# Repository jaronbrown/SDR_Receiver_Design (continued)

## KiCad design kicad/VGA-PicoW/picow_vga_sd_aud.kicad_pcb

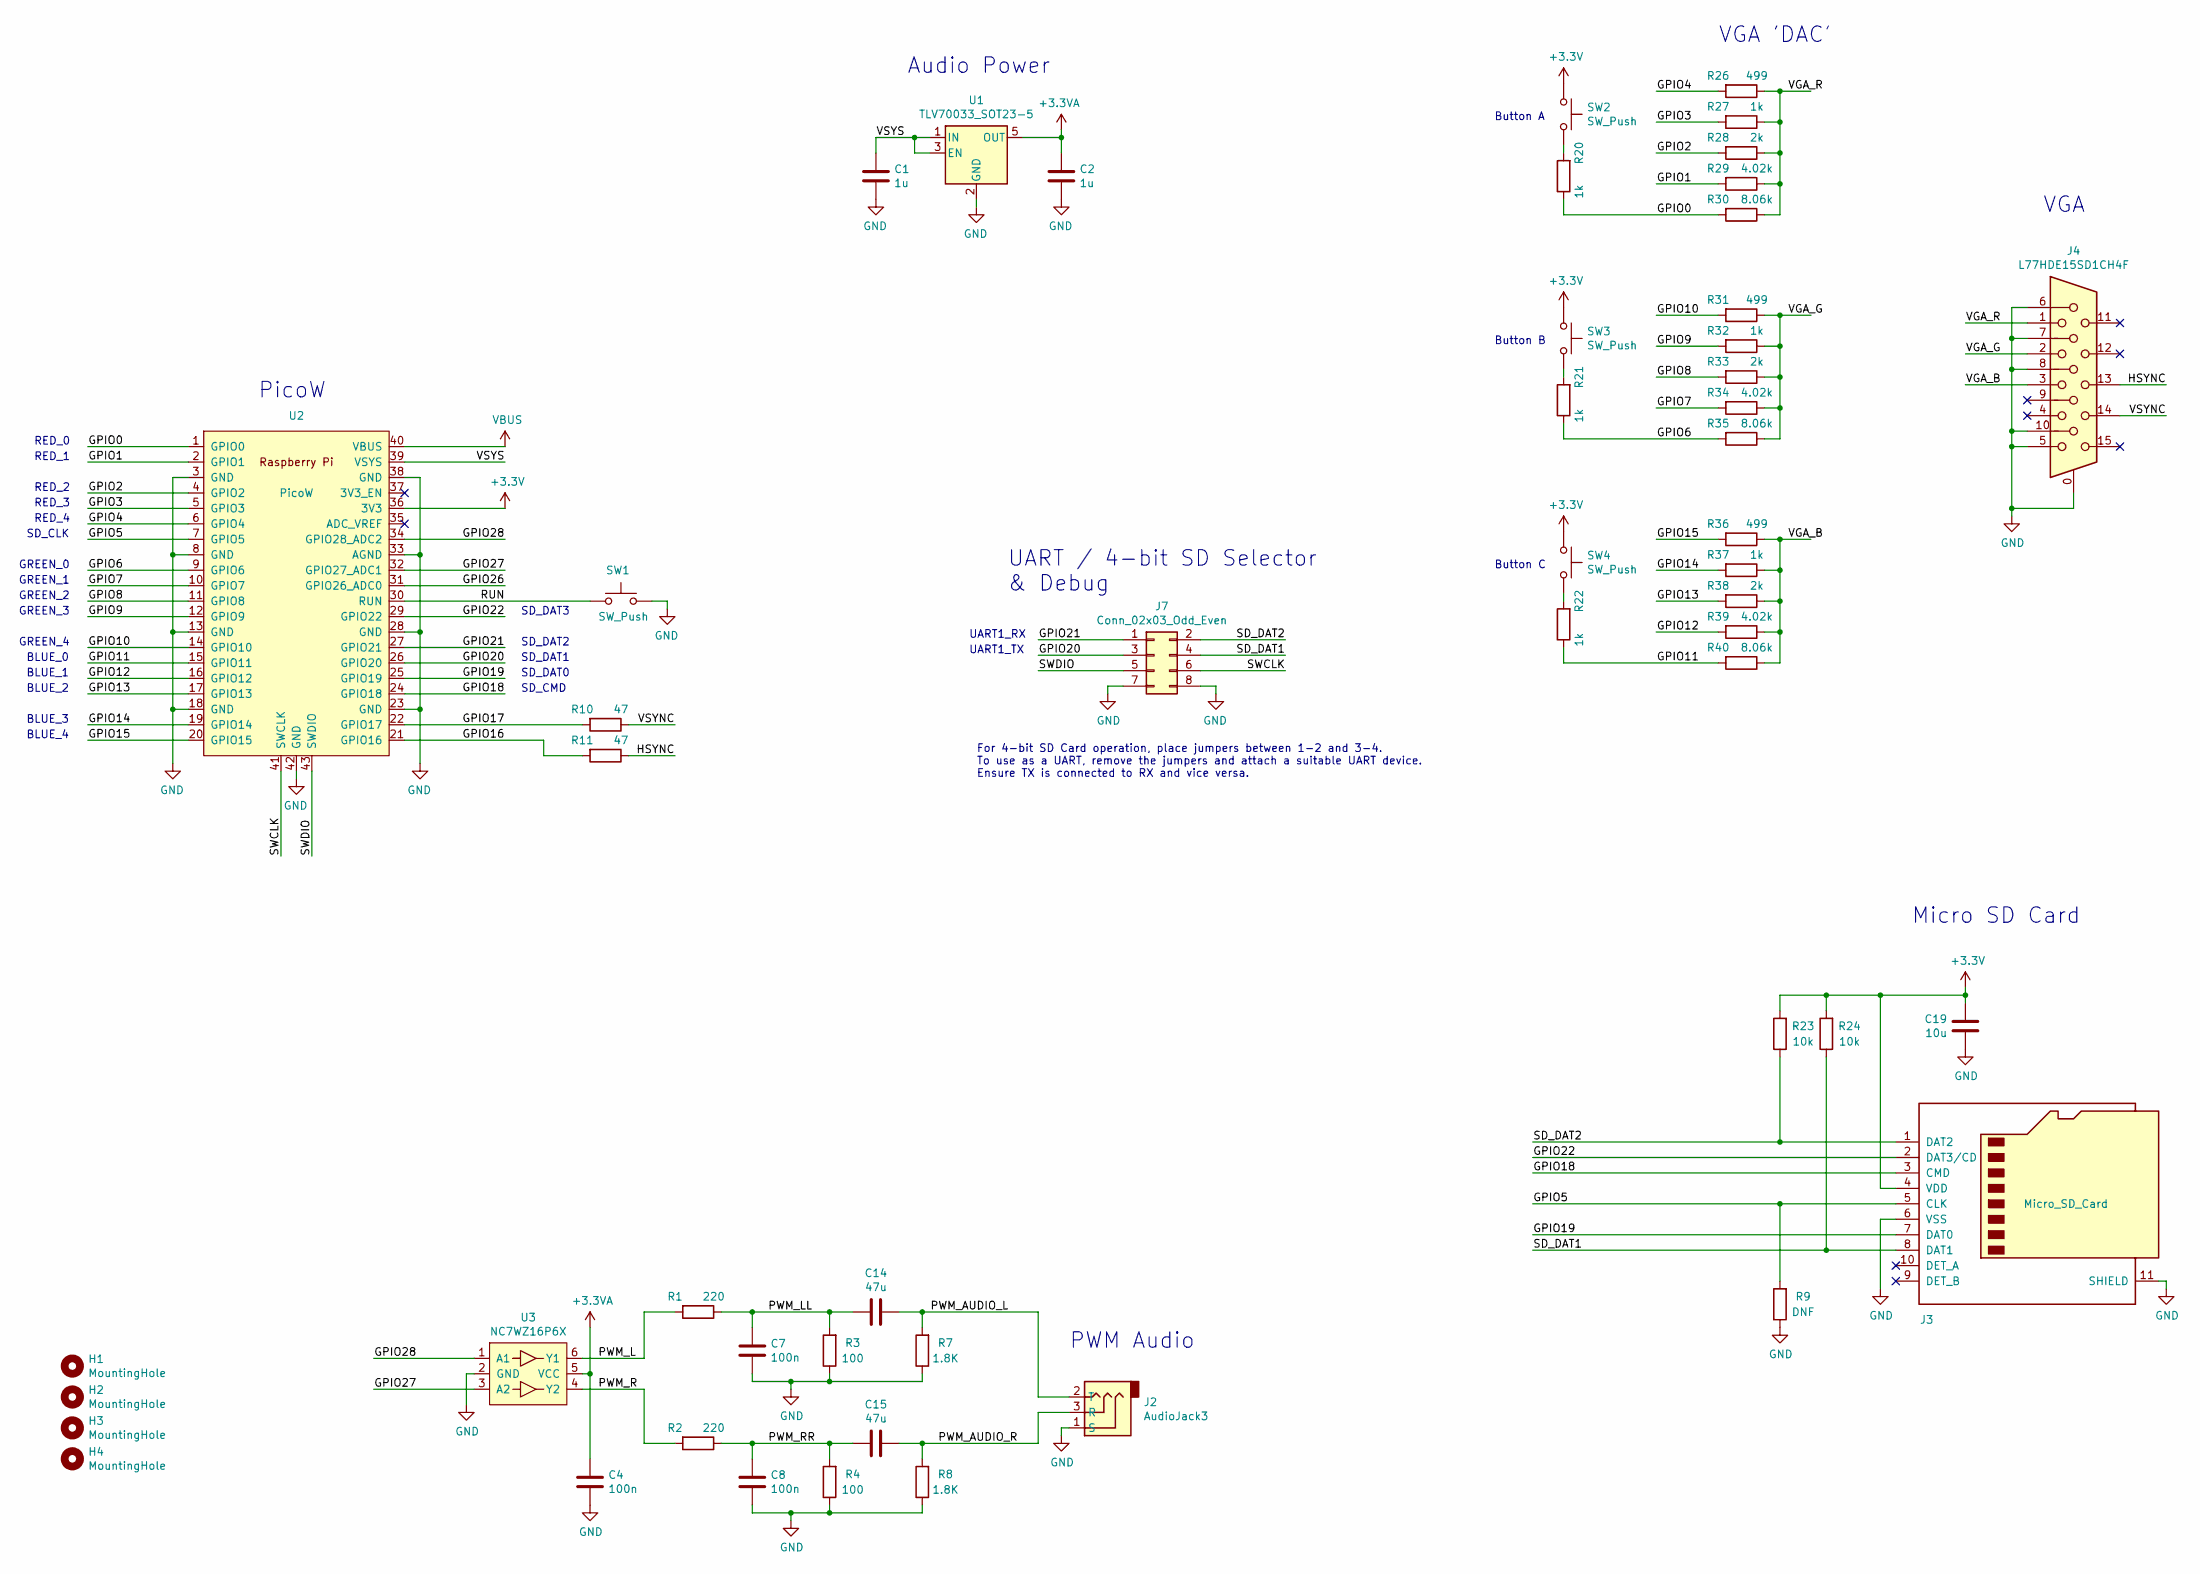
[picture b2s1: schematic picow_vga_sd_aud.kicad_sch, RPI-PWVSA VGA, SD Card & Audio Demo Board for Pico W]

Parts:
C1, C2: 1u; C_0603_1608Metric
C4, C7, C8: 100n; C_0402_1005Metric
C14, C15: 47u; C_0805_2012Metric
C19: 10u; C_0603_1608Metric
H1, H2, H3, H4: MountingHole; MountingHole_2.7mm_M2.5
J2: AudioJack3; CUI_SJ-3523-audio-jack
J3: Micro_SD_Card; microSD_HC_Molex_104031-0811
J4: L77HDE15SD1CH4F; DSUB-15-L77HDE15SD1CH4F
J7: Conn_02x03_Odd_Even; PinHeader_2x04_P2.54mm_Vertical
R1, R2: 220; R_0402_1005Metric
R3, R4: 100; R_0402_1005Metric
R7, R8: 1.8K; R_0402_1005Metric
R9: DNF; R_0402_1005Metric
R10, R11: 47; R_0402_1005Metric
R20, R21, R22, R27, R32, R37: 1k; R_0402_1005Metric
R23, R24: 10k; R_0402_1005Metric
R26, R31, R36: 499; R_0402_1005Metric
R28, R33, R38: 2k; R_0402_1005Metric
R29, R34, R39: 4.02k; R_0402_1005Metric
R30, R35, R40: 8.06k; R_0402_1005Metric
SW1, SW2, SW3, SW4: SW_Push; SW_Push_1P1T_NO_Vertical_Wuerth_434133025816
U1: TLV70033_SOT23-5; SOT-23-5
U2: PicoW; RPi_PicoW_SMD_TH
U3: NC7WZ16P6X; SOT-363_SC-70-6

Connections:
+3.3VA: C2.1, C4.1, U1.5 (OUT), U3.5 (VCC)
+3V3: C19.1, J3.4 (VDD), R23.2, R24.2, SW2.1, SW3.1, SW4.1, U2.36 (3V3)
/GPIO0: R20.1, R30.2, U2.1 (GPIO0)
/GPIO1: R29.2, U2.2 (GPIO1)
/GPIO2: R28.2, U2.4 (GPIO2)
/GPIO3: R27.2, U2.5 (GPIO3)
/GPIO4: R26.2, U2.6 (GPIO4)
/GPIO5: J3.5 (CLK), R9.2, U2.7 (GPIO5)
/GPIO6: R21.1, R35.2, U2.9 (GPIO6)
/GPIO7: R34.2, U2.10 (GPIO7)
/GPIO8: R33.2, U2.11 (GPIO8)
/GPIO9: R32.2, U2.12 (GPIO9)
/GPIO10: R31.2, U2.14 (GPIO10)
/GPIO11: R22.1, R40.2, U2.15 (GPIO11)
/GPIO12: R39.2, U2.16 (GPIO12)
/GPIO13: R38.2, U2.17 (GPIO13)
/GPIO14: R37.2, U2.19 (GPIO14)
/GPIO15: R36.2, U2.20 (GPIO15)
/GPIO16: R11.2, U2.21 (GPIO16)
/GPIO17: R10.2, U2.22 (GPIO17)
/GPIO18: J3.3 (CMD), U2.24 (GPIO18)
/GPIO19: J3.7 (DAT0), U2.25 (GPIO19)
/GPIO20: J7.3, U2.26 (GPIO20)
/GPIO21: J7.1, U2.27 (GPIO21)
/GPIO22: J3.2 (DAT3/CD), U2.29 (GPIO22)
/GPIO26: U2.31 (GPIO26_ADC0)
/GPIO27: U2.32 (GPIO27_ADC1), U3.3 (A2)
/GPIO28: U2.34 (GPIO28_ADC2), U3.1 (A1)
/HSYNC: J4.13, R11.1
/PWM_AUDIO_L: C14.1, J2.2 (T), R7.2
/PWM_AUDIO_R: C15.1, J2.3 (R), R8.2
/PWM_L: R1.2, U3.6 (Y1)
/PWM_LL: C7.1, C14.2, R1.1, R3.2
/PWM_R: R2.2, U3.4 (Y2)
/PWM_RR: C8.1, C15.2, R2.1, R4.2
/RUN: SW1.1, U2.30 (RUN)
/SD_DAT1: J3.8 (DAT1), J7.4, R24.1
/SD_DAT2: J3.1 (DAT2), J7.2, R23.1
/SWCLK: J7.6, U2.41 (SWCLK)
/SWDIO: J7.5, U2.43 (SWDIO)
/VGA_B: J4.3, R36.1, R37.1, R38.1, R39.1, R40.1
/VGA_G: J4.2, R31.1, R32.1, R33.1, R34.1, R35.1
/VGA_R: J4.1, R26.1, R27.1, R28.1, R29.1, R30.1
/VSYNC: J4.14, R10.1
/VSYS: C1.1, U1.1 (IN), U1.3 (EN), U2.39 (VSYS)
GND: C1.2, C2.2, C4.2, C7.2, C8.2, C19.2, J2.1 (S), J3.6 (VSS), J3.11 (SHIELD), J4.0, J4.5, J4.6, J4.7, J4.8, J4.10, J7.7, J7.8, R3.1, R4.1, R7.1, R8.1, R9.1, SW1.2, U1.2 (GND), U2.3 (GND), U2.8 (GND), U2.13 (GND), U2.18 (GND), U2.23 (GND), U2.28 (GND), U2.33 (AGND), U2.38 (GND), U2.42 (GND), U3.2 (GND)
unnamed: R20.2, SW2.2
unnamed: R21.2, SW3.2
unnamed: R22.2, SW4.2
VBUS: U2.40 (VBUS)

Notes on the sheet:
GREEN_0
RED_3
RED_1
SD_DAT2
Button A
VGA
SD_CLK
BLUE_4
BLUE_0
UART1_TX
SD_DAT1
RED_4
PicoW
For 4-bit SD Card operation, place jumpers between 1-2 and 3-4. To use as a UART, remove the jumpers and attach a suitable UART device. Ensure TX is connected to RX and vice versa.
UART1_RX
VGA 'DAC'
Button B
Button C
GREEN_1
UART / 4-bit SD Selector & Debug
SD_DAT0
BLUE_3
SD_CMD
SD_DAT3
Micro SD Card
GREEN_4
RED_2
GREEN_2
Audio Power
PWM Audio
BLUE_1
GREEN_3
BLUE_2
RED_0

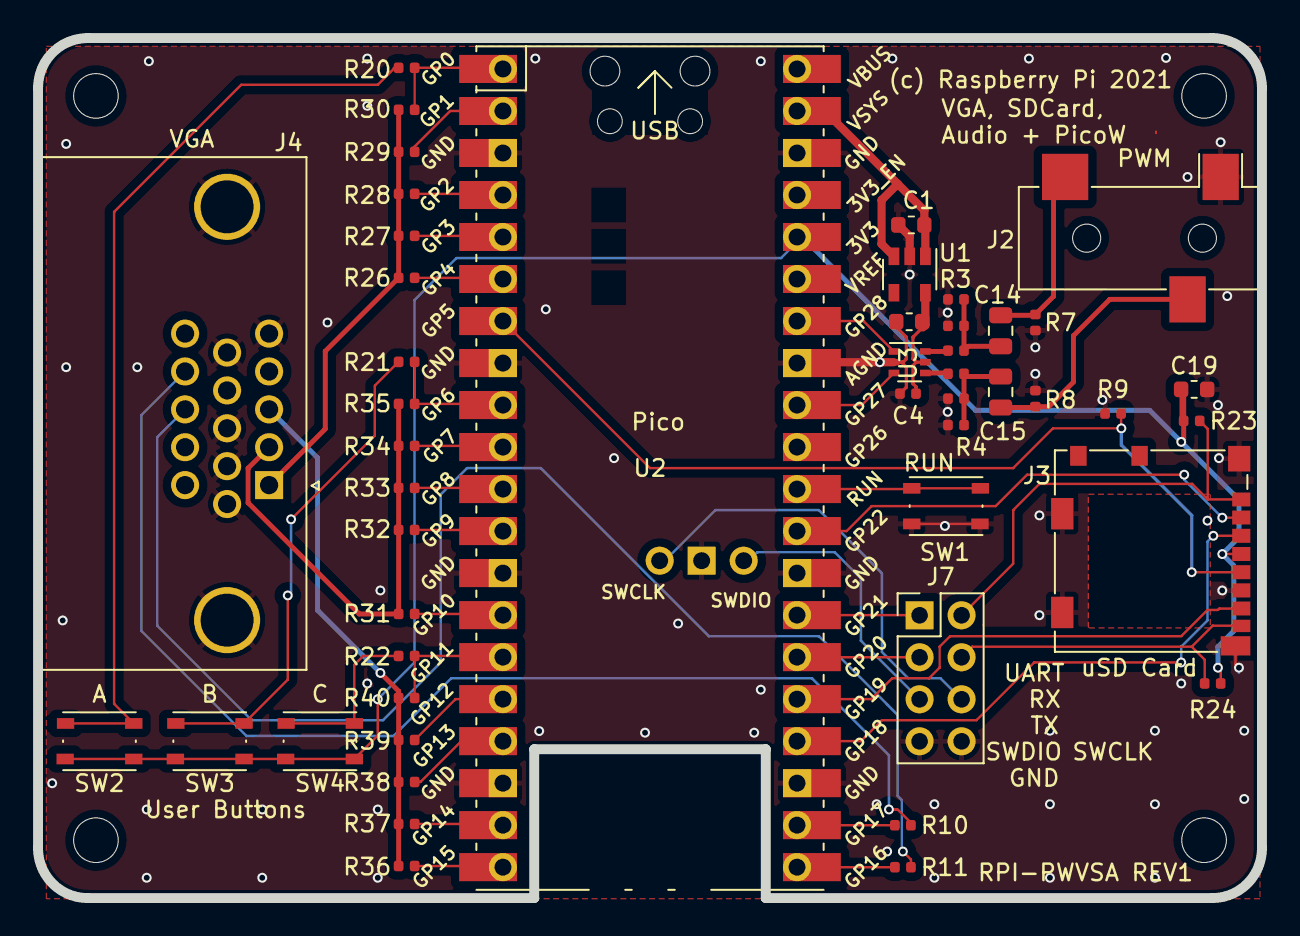
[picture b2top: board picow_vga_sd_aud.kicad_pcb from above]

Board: 4 copper layers, 74.0 x 52.0 mm, 52 parts (0 on the bottom side), 48 nets.

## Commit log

2024-04-02 Trying to get rid of .raw files
2024-06-07 clean
2024-06-07 orphan
